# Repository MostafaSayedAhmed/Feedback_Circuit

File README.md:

# Feedback Circuit

## Overview
This PCB is designed to test the functionality of each terminal block on an upper distribution board. It provides a simple yet efficient method to verify the electrical connectivity and correct operation of all connected terminal blocks.

## Features
- **Terminal Block Testing**: Ensures proper connection and functionality of terminal blocks.
- **Status Indicators**: LED indicators provide visual feedback for the testing process.
- **Power Management**: Integrated DC step-down module to regulate power input.
- **Compact Design**: Efficient layout to streamline testing processes.

## Board Components
### Key Elements:
- **Terminal Blocks**: Testing points connected to the upper distribution board.
- **LED Indicators**: Visual feedback for terminal block status.
- **DC-DC Step-Down Converter**: Converts input voltage (e.g., 12V) to operating voltage levels (e.g., 5V, 3.3V) for board operation.
- **Resistors (R1 - R50)**: Used for current-limiting and other circuit purposes.
- **Connectors**: Input/output interfaces for connecting the board to the upper distribution board.

## How to Use
1. **Power Up**:
   - Connect a 12V power supply to the board's main input terminals.
   - Ensure the DC-DC step-down module regulates the voltage properly to the required levels (e.g., 5V or 3.3V).

2. **Connect Upper Distribution Board**:
   - Plug the terminal blocks from the upper distribution board into the corresponding slots on this PCB.

3. **Verify Connections**:
   - Each terminal block's status is indicated by the corresponding LED. 
   - A lit LED indicates proper connectivity and function.

4. **Debugging**:
   - If an LED does not light up, inspect the terminal block connection and associated circuitry.

## Technical Specifications
- **Input Voltage**: 12V DC
- **Output Voltage**: 5V, 3.3V (regulated via step-down module)
- **Indicators**: LEDs for testing status
- **Supported Protocols**: Compatible with terminal blocks of various configurations

## Applications
- Functional testing of terminal blocks on distribution boards.
- Diagnostic tool for debugging electrical connections in larger systems.

## Notes
- Ensure correct polarity when connecting the power supply.
- Always inspect the board for physical damage or misaligned components before use.
- Disconnect power before making any hardware adjustments.

## License
This project is open-source. You may modify or distribute it as needed under the terms of the MIT License.

---

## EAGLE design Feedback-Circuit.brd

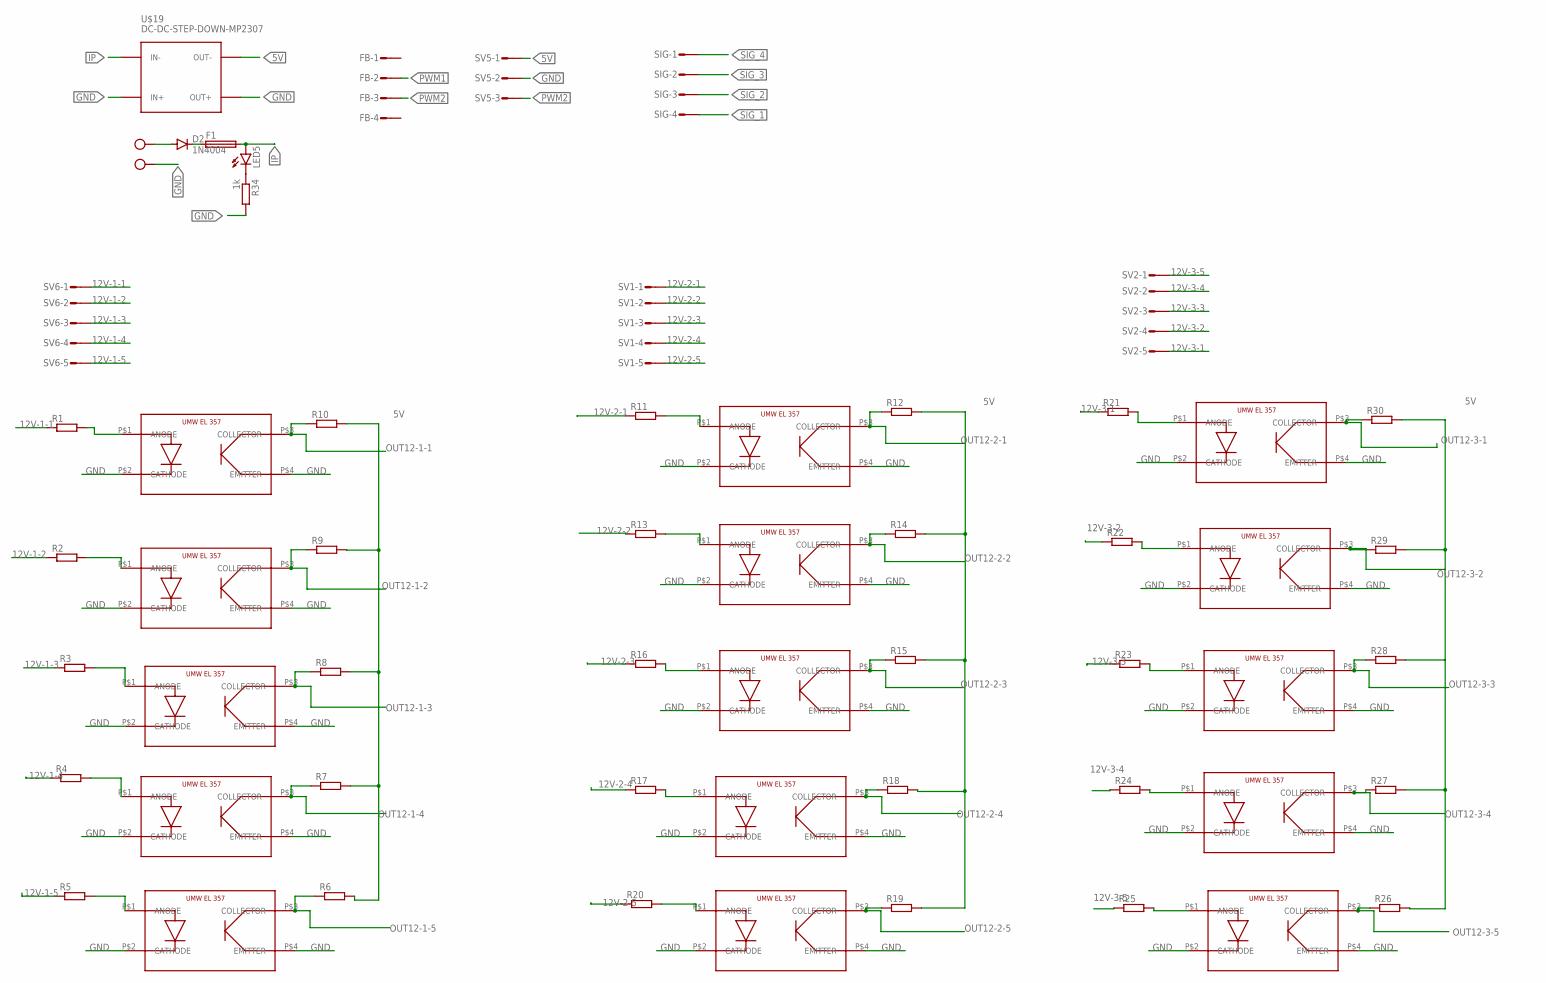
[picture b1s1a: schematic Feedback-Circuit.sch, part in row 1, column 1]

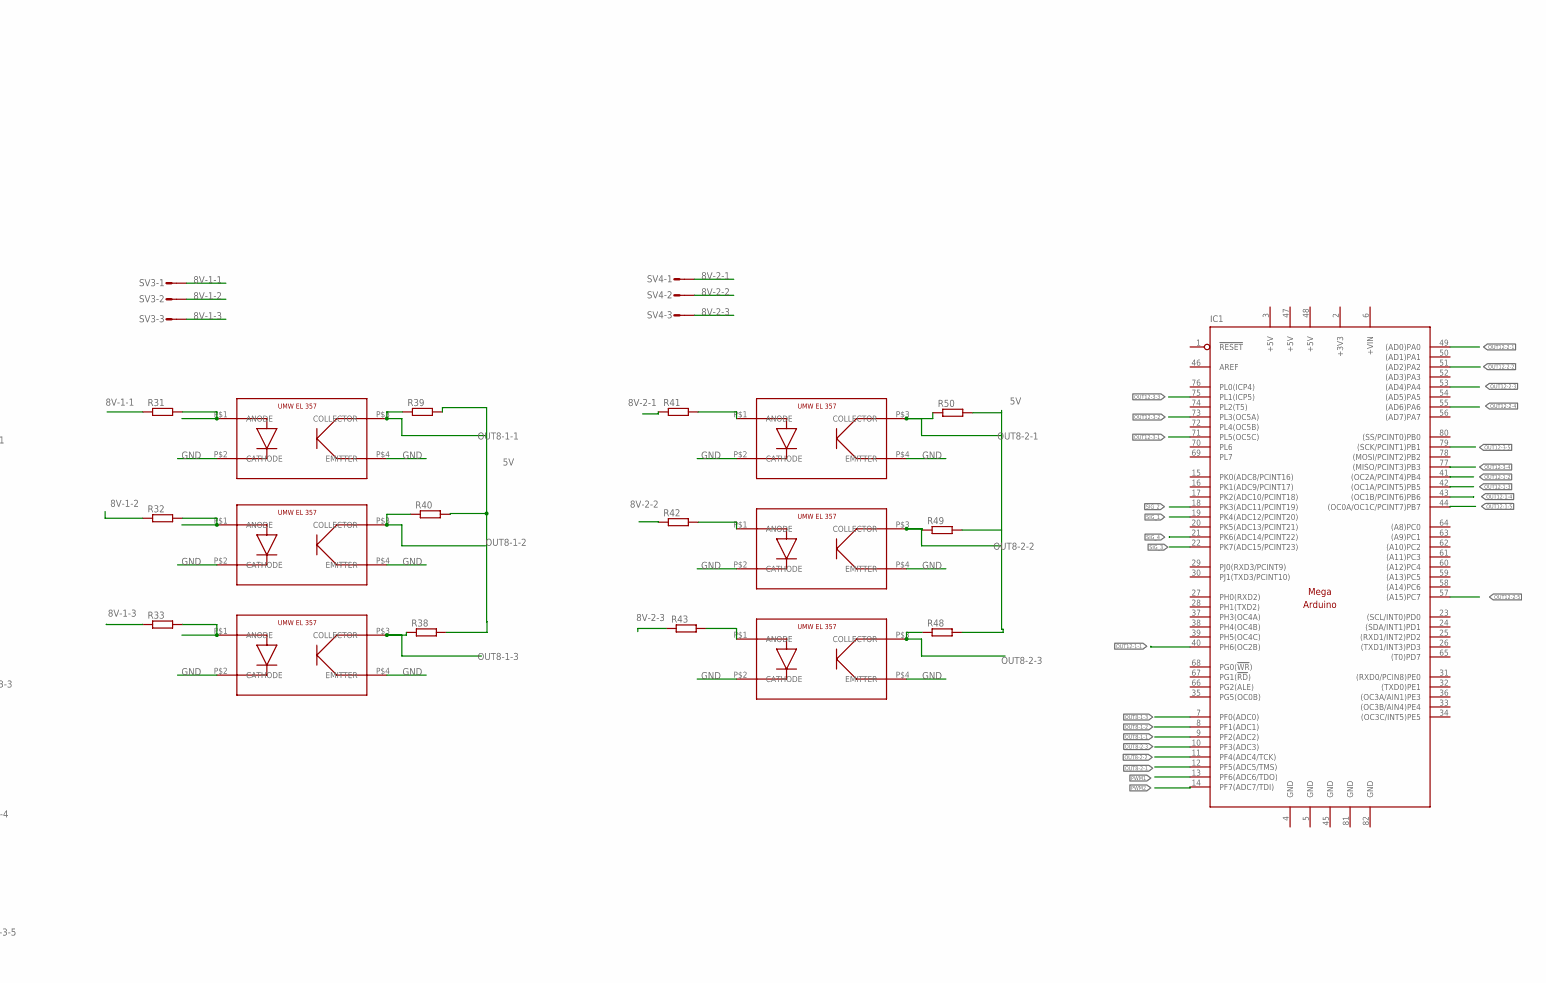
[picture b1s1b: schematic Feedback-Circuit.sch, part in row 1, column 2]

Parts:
D2: 1N4004; DO41-10
F1: FUSE_SH22
FB: CON-AMP-MT_S04P
IC1: MEGAARDUINO_1; MEGA_ARDUINO
LED5: LED3MM
MAIN-12V: AK300/2
R1, R2, R3, R4, R5, R6, R7, R8, R9, R10, R11, R12, R13, R14, R15, R16, R17, R18, R19, R20, R21, R22, R23, R24, R25, R26, R27, R28, R29, R30, R31, R32, R33, R38, R39, R40, R41, R42, R43, R48, R49, R50: R-EU_R1206W; R1206W
R34: 1k; 0207/10
SIG: CON-AMP-MT_S04P
SV1, SV2, SV3, SV4, SV6: CON-AMP-MT_S05P
SV5: CON-AMP-MT_S03P
U$1, U$2, U$3, U$4, U$5, U$6, U$7, U$8, U$9, U$10, U$11, U$12, U$13, U$14, U$15, U$16, U$17, U$18, U$21, U$22, U$23: UMWEL357EL357; OPTOCOUPLER
U$19: DC-DC-STEP-DOWN-MP2307

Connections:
5V: R6.2, R7.2, R8.2, R9.2, R10.2, R12.2, R14.2, R15.2, R18.2, R19.2, R26.2, R27.2, R28.2, R29.2, R30.2, R38.2, R39.2, R40.2, R48.2, R49.2, R50.2, SV5.1, U$19.OUT-
8V-1-1: R31.1, SV3.1
8V-1-2: R32.1, SV3.2
8V-1-3: R33.1, SV3.3
8V-2-1: R41.1, SV4.1
8V-2-2: R42.1, SV4.2
8V-2-3: R43.1, SV4.3
12V: D2.A, MAIN-12V.1
12V-1-1: R1.1, SV6.1
12V-1-2: R2.1, SV6.2
12V-1-3: R3.1, SV6.3
12V-1-4: R4.1, SV6.4
12V-1-5: R5.1, SV6.5
12V-2-1: R11.1, SV1.1
12V-2-2: R13.1, SV1.2
12V-2-3: R16.1, SV1.3
12V-2-4: R17.1, SV1.4
12V-2-5: R20.1, SV1.5
12V-3-1: R21.1, SV2.5
12V-3-2: R22.1, SV2.4
12V-3-3: R23.1, SV2.3
12V-3-4: R24.1, SV2.2
12V-3-5: R25.1, SV2.1
+3V3: IC1.2 (+3V3)
+5V: IC1.3 (+5V), IC1.47 (+5V), IC1.48 (+5V)
+VIN: IC1.6 (+VIN)
GND: IC1.4 (GND), IC1.5 (GND), IC1.45 (GND), IC1.81 (GND), IC1.82 (GND), MAIN-12V.2, R34.2, SV5.2, U$1.P$2 (CATHODE), U$1.P$4 (EMITTER), U$2.P$2 (CATHODE), U$2.P$4 (EMITTER), U$3.P$2 (CATHODE), U$3.P$4 (EMITTER), U$4.P$2 (CATHODE), U$4.P$4 (EMITTER), U$5.P$2 (CATHODE), U$5.P$4 (EMITTER), U$6.P$2 (CATHODE), U$6.P$4 (EMITTER), U$7.P$2 (CATHODE), U$7.P$4 (EMITTER), U$8.P$2 (CATHODE), U$8.P$4 (EMITTER), U$9.P$2 (CATHODE), U$9.P$4 (EMITTER), U$10.P$2 (CATHODE), U$10.P$4 (EMITTER), U$11.P$2 (CATHODE), U$11.P$4 (EMITTER), U$12.P$2 (CATHODE), U$12.P$4 (EMITTER), U$13.P$2 (CATHODE), U$13.P$4 (EMITTER), U$14.P$2 (CATHODE), U$14.P$4 (EMITTER), U$15.P$2 (CATHODE), U$15.P$4 (EMITTER), U$16.P$2 (CATHODE), U$16.P$4 (EMITTER), U$17.P$2 (CATHODE), U$17.P$4 (EMITTER), U$18.P$2 (CATHODE), U$18.P$4 (EMITTER), U$19.IN+, U$19.OUT+, U$21.P$2 (CATHODE), U$21.P$4 (EMITTER), U$22.P$2 (CATHODE), U$22.P$4 (EMITTER), U$23.P$2 (CATHODE), U$23.P$4 (EMITTER)
IP: F1.2, LED5.A, U$19.IN-
unnamed: R11.2, U$6.P$1 (ANODE)
unnamed: R2.2, U$2.P$1 (ANODE)
unnamed: R3.2, U$3.P$1 (ANODE)
unnamed: R1.2, U$1.P$1 (ANODE)
unnamed: R4.2, U$4.P$1 (ANODE)
unnamed: R5.2, U$5.P$1 (ANODE)
unnamed: R13.2, U$7.P$1 (ANODE)
unnamed: R16.2, U$8.P$1 (ANODE)
unnamed: R17.2, U$9.P$1 (ANODE)
unnamed: R20.2, U$10.P$1 (ANODE)
unnamed: R21.2, U$11.P$1 (ANODE)
unnamed: R22.2, U$12.P$1 (ANODE)
unnamed: R23.2, U$13.P$1 (ANODE)
unnamed: R24.2, U$14.P$1 (ANODE)
unnamed: R25.2, U$15.P$1 (ANODE)
unnamed: R41.2, U$21.P$1 (ANODE)
unnamed: R42.2, U$22.P$1 (ANODE)
unnamed: R43.2, U$23.P$1 (ANODE)
unnamed: R31.2, U$16.P$1 (ANODE)
unnamed: R32.2, U$17.P$1 (ANODE)
unnamed: R33.2, U$18.P$1 (ANODE)
unnamed: LED5.K (C), R34.1
unnamed: D2.C, F1.1
OUT8-1-1: IC1.9 (PF2(ADC2)), R39.1, U$16.P$3 (COLLECTOR)
OUT8-1-2: IC1.8 (PF1(ADC1)), R40.1, U$17.P$3 (COLLECTOR)
OUT8-1-3: IC1.7 (PF0(ADC0)), R38.1, U$18.P$3 (COLLECTOR)
OUT8-2-1: IC1.12 (PF5(ADC5/TMS)), R50.1, U$21.P$3 (COLLECTOR)
OUT8-2-2: IC1.11 (PF4(ADC4/TCK)), R49.1, U$22.P$3 (COLLECTOR)
OUT8-2-3: IC1.10 (PF3(ADC3)), R48.1, U$23.P$3 (COLLECTOR)
OUT12-1-1: IC1.40 (PH6(OC2B)), R10.1, U$1.P$3 (COLLECTOR)
OUT12-1-2: IC1.41 ((OC2A/PCINT4)PB4), R9.1, U$2.P$3 (COLLECTOR)
OUT12-1-3: IC1.42 ((OC1A/PCINT5)PB5), R8.1, U$3.P$3 (COLLECTOR)
OUT12-1-4: IC1.43 ((OC1B/PCINT6)PB6), R7.1, U$4.P$3 (COLLECTOR)
OUT12-1-5: IC1.44 ((OC0A/OC1C/PCINT7)PB7), R6.1, U$5.P$3 (COLLECTOR)
OUT12-2-1: IC1.49 ((AD0)PA0), R12.1, U$6.P$3 (COLLECTOR)
OUT12-2-2: IC1.51 ((AD2)PA2), R14.1, U$7.P$3 (COLLECTOR)
OUT12-2-3: IC1.53 ((AD4)PA4), R15.1, U$8.P$3 (COLLECTOR)
OUT12-2-4: IC1.55 ((AD6)PA6), R18.1, U$9.P$3 (COLLECTOR)
OUT12-2-5: IC1.57 ((A15)PC7), R19.1, U$10.P$3 (COLLECTOR)
OUT12-3-1: IC1.71 (PL5(OC5C)), R30.1, U$11.P$3 (COLLECTOR)
OUT12-3-2: IC1.73 (PL3(OC5A)), R29.1, U$12.P$3 (COLLECTOR)
OUT12-3-3: IC1.75 (PL1(ICP5)), R28.1, U$13.P$3 (COLLECTOR)
OUT12-3-4: IC1.77 ((MISO/PCINT3)PB3), R27.1, U$14.P$3 (COLLECTOR)
OUT12-3-5: IC1.79 ((SCK/PCINT1)PB1), R26.1, U$15.P$3 (COLLECTOR)
PWM1: FB.2, IC1.13 (PF6(ADC6/TDO))
PWM2: FB.3, IC1.14 (PF7(ADC7/TDI)), SV5.3
SIG_1: IC1.19 (PK4(ADC12/PCINT20)), SIG.4
SIG_2: IC1.18 (PK3(ADC11/PCINT19)), SIG.3
SIG_3: IC1.22 (PK7(ADC15/PCINT23)), SIG.2
SIG_4: IC1.21 (PK6(ADC14/PCINT22)), SIG.1

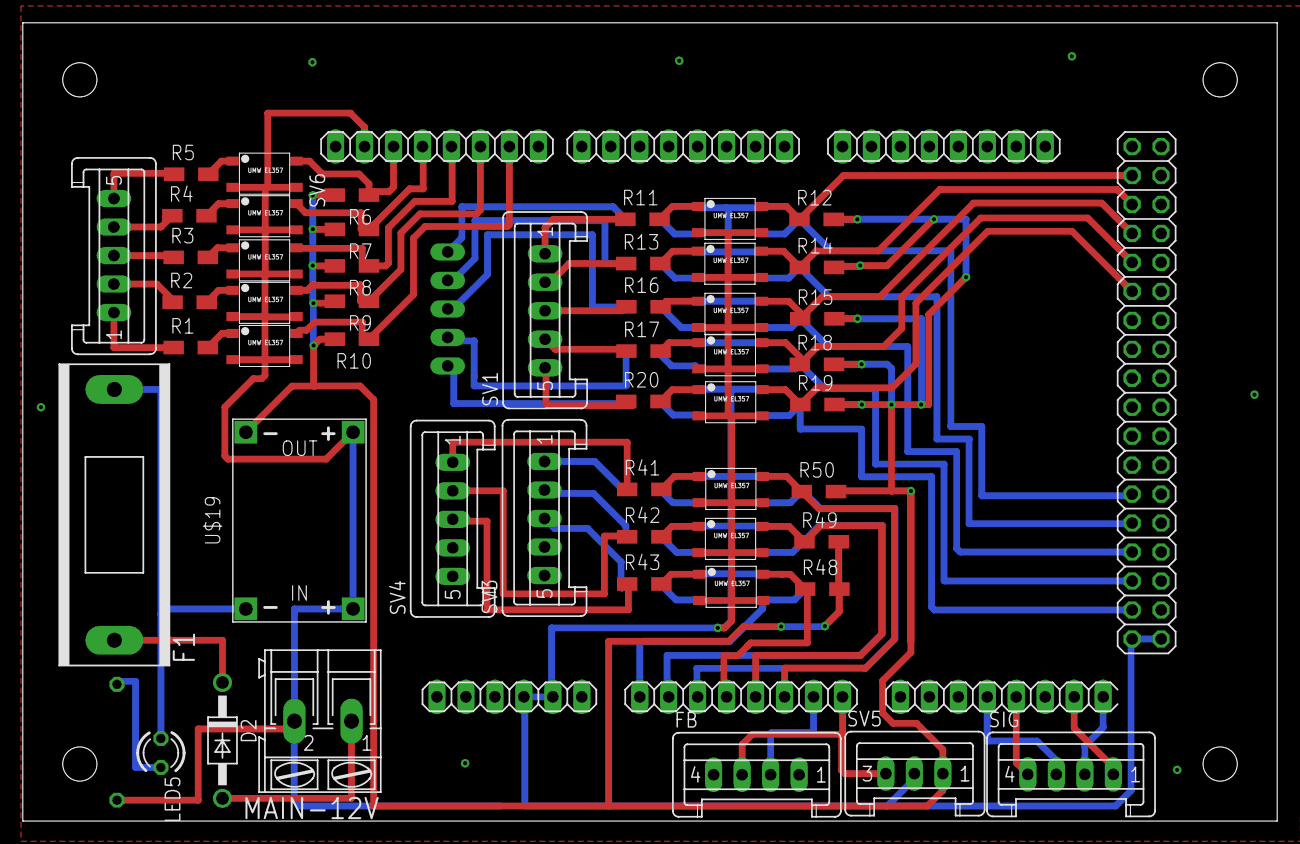
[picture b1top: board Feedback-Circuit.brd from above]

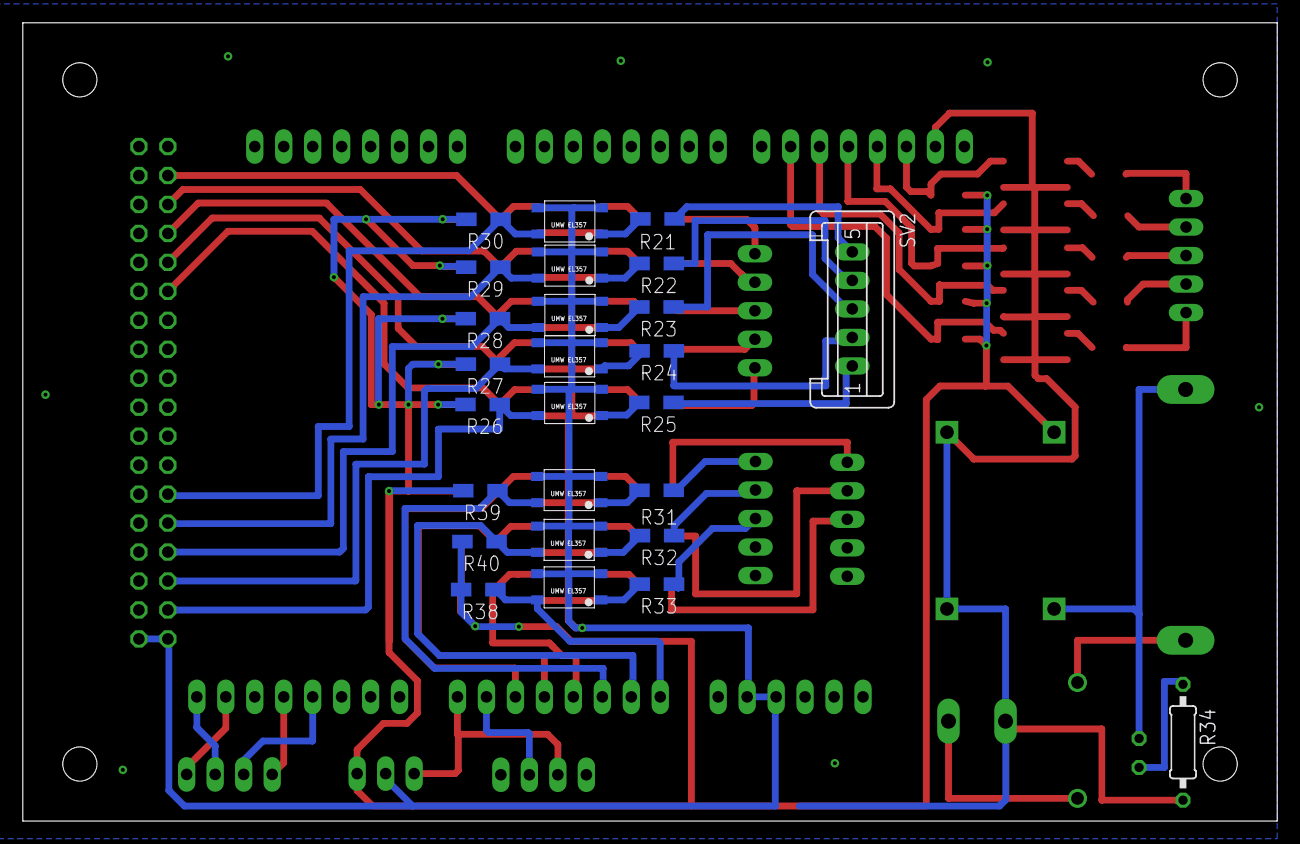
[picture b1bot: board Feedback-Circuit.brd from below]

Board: 2 copper layers, 110.0 x 70.0 mm, 78 parts (26 on the bottom side), 76 nets.

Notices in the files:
parts and their libraries:
buck 3A: Released under the Creative Commons Attribution 4.0 International License: http://creativecommons.org/licenses/by/4.0
